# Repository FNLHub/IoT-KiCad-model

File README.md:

# IoT-KiCad-model
KiCad schematics for fan controller circuit

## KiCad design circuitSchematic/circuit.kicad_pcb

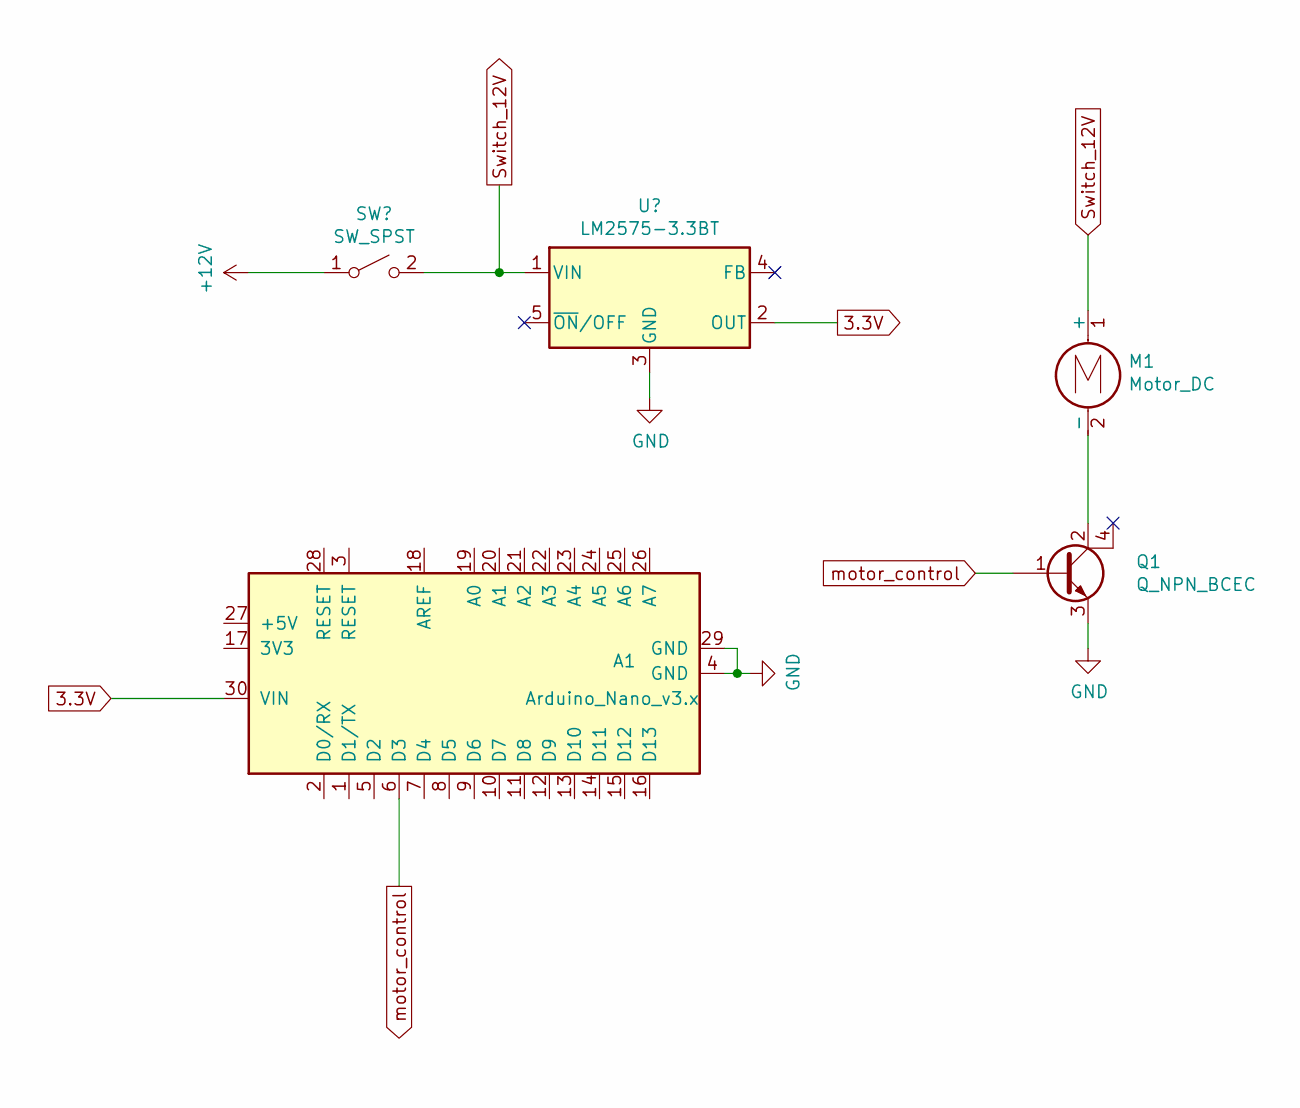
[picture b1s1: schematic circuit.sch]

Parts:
A1: Arduino_Nano_v3.x; Arduino_Nano
M1: Motor_DC; PinHeader_1x03_P2.54mm_Vertical
Q1: Q_NPN_BCEC; TO-220-3_Horizontal_TabDown

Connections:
+12V: M1.1 (+)
GND: A1.4 (GND), A1.29 (GND), Q1.3 (E)
unnamed: M1.2 (-), Q1.2 (C)
motor_control: A1.6 (D3), Q1.1 (B)

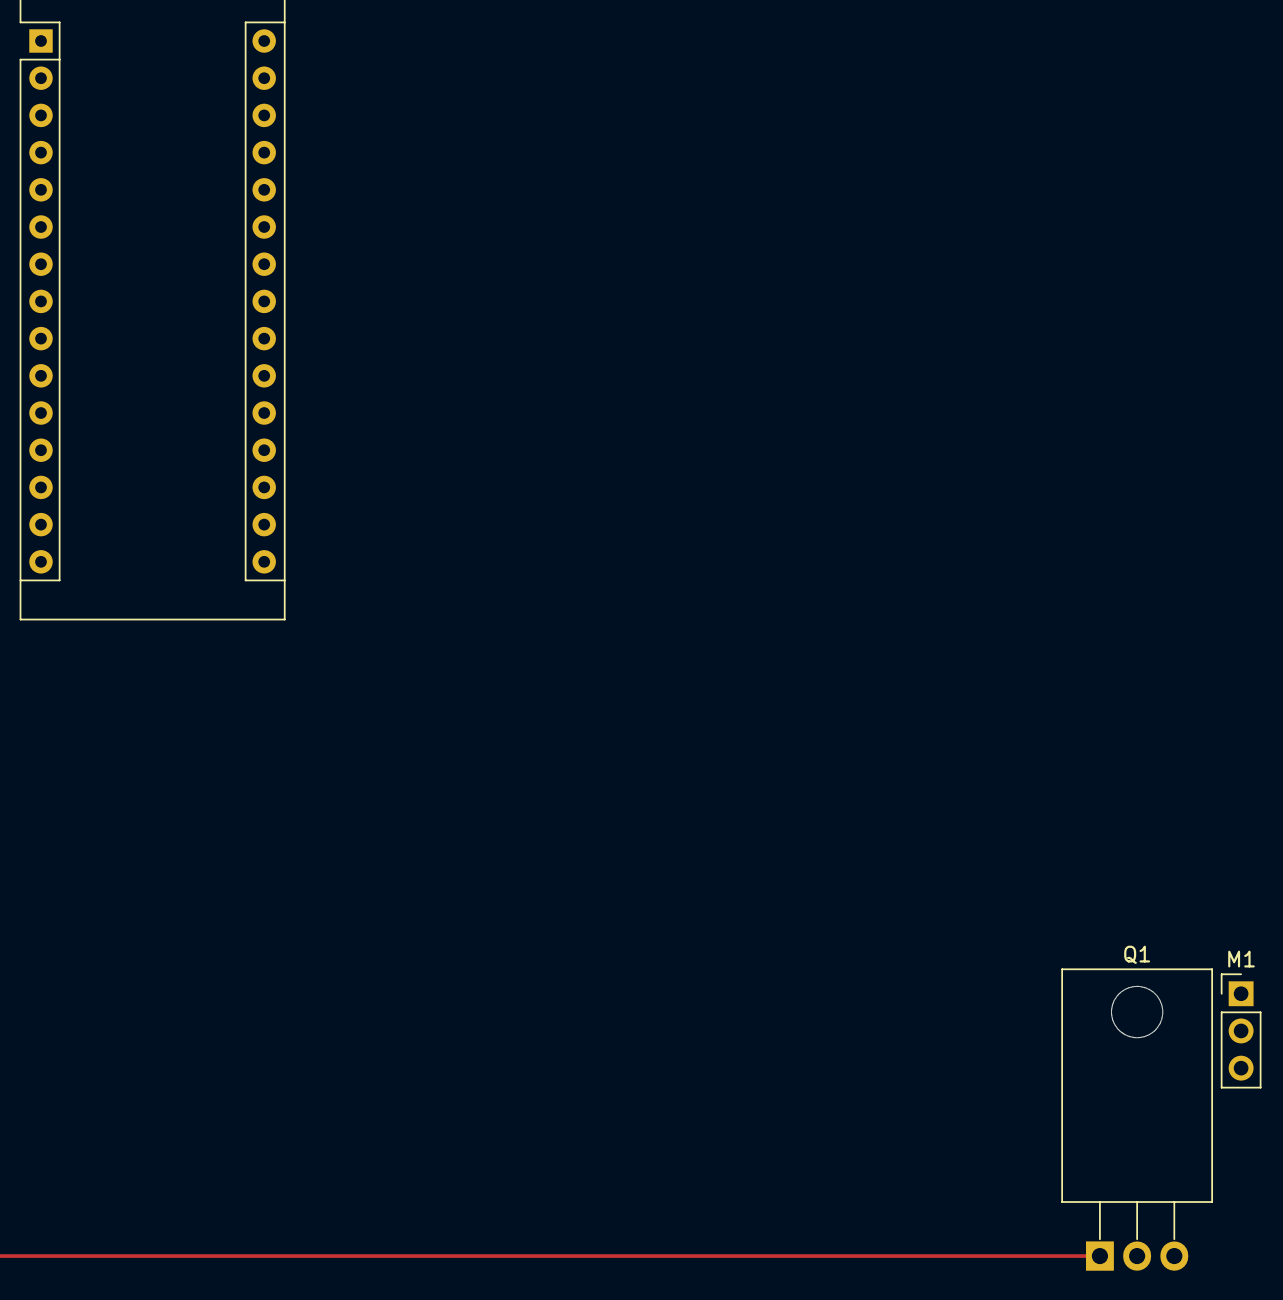
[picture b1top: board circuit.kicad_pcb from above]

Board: 2 copper layers, 3 parts (0 on the bottom side), 3 nets.

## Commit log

2019-02-23 Added KiCad model of project's circuit
2019-02-23 fixed ambigous naming of some files
2019-03-01 Updated Vin voltage value, from 3.3V to 5V
2019-03-02 Fixed output pin from D3 to D7 and added indicator LED to pin D6
2019-03-10 moved stuff around for readablity
